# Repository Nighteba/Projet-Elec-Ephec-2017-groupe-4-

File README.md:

# Projet-Elec-Ephec-2017-groupe-4-
Projet d'électro

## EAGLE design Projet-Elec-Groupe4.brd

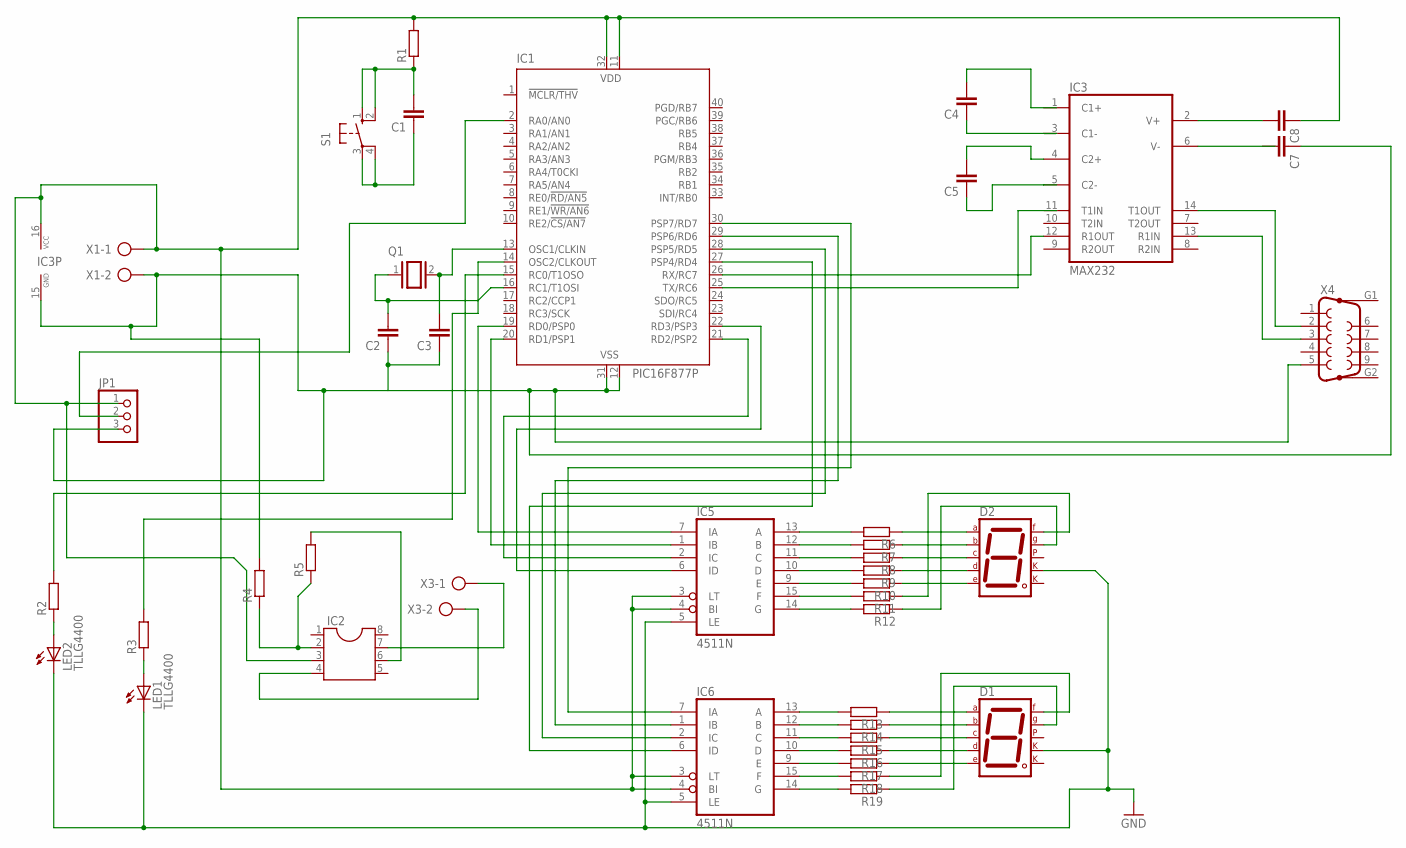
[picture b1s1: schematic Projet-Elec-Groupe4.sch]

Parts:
C1: C-EU025-025X050; C025-025X050
C2, C3, C4, C5, C7, C8: C-EU025-024X044; C025-024X044
D1, D2: 7SEG-CK; 7SEG-13
IC1: PIC16F877P; DIL40
IC2: DIL8; DIL08
IC3: MAX232; DIL16
IC5, IC6: 4511N; DIL16
JP1: PINHD-1X3; 1X03
LED1, LED2: TLLG4400; LED3MM
Q1: XTAL/S; QS
R1, R2, R3, R4, R5, R6, R7, R8, R9, R10, R11, R12, R13, R14, R15, R16, R17, R18, R19: R-EU_0207/10; 0207/10
S1: 10-XX; B3F-10XX
X1, X3: AK300/2
X4: F09HP

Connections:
GND: D1.3 (CK1), D2.3 (CK1), IC5.5 (LE), IC6.5 (LE), LED1.K (C), LED2.K (C)
unnamed: C5.2, IC3.4 (C2+)
unnamed: C2.2, IC1.14 (OSC2/CLKOUT), Q1.1
unnamed: C8.1, IC1.11 (VDD), IC1.32 (VDD), IC2.3, IC3.16 (VCC), IC5.3 (LT), IC5.4 (BI), IC6.3 (LT), IC6.4 (BI), JP1.1, R1.2, X1.1
unnamed: C1.2, R1.1, S1.1 (S), S1.2 (S1)
unnamed: C1.1, S1.3, S1.4 (P1)
unnamed: C5.1, IC3.5 (C2-)
unnamed: C3.2, IC1.13 (OSC1/CLKIN), Q1.2
unnamed: IC1.2 (RA0/AN0), JP1.2
unnamed: IC1.26 (RX/RC7), IC3.12 (R1OUT)
unnamed: IC3.14 (T1OUT), X4.2
unnamed: IC3.13 (R1IN), X4.3
unnamed: C4.1, IC3.3 (C1-)
unnamed: C8.2, IC3.2 (V+)
unnamed: IC5.13 (A), R6.2
unnamed: D2.7 (A), R6.1
unnamed: IC5.12 (B), R7.2
unnamed: D2.6 (B), R7.1
unnamed: IC5.11 (C), R8.2
unnamed: D2.9 (F), R11.1
unnamed: D2.10 (G), R12.1
unnamed: IC2.7, X3.1
unnamed: IC1.19 (RD0/PSP0), IC5.7 (IA)
unnamed: IC1.20 (RD1/PSP1), IC5.1 (IB)
unnamed: IC1.21 (RD2/PSP2), IC5.2 (IC)
unnamed: IC1.22 (RD3/PSP3), IC5.6 (ID)
unnamed: IC6.13 (A), R13.2
unnamed: D1.7 (A), R13.1
unnamed: D1.6 (B), R14.1
unnamed: IC6.12 (B), R14.2
unnamed: IC6.11 (C), R15.2
unnamed: IC1.27 (PSP4/RD4), IC6.6 (ID)
unnamed: IC1.28 (PSP5/RD5), IC6.2 (IC)
unnamed: IC1.29 (PSP6/RD6), IC6.1 (IB)
unnamed: IC1.30 (PSP7/RD7), IC6.7 (IA)
unnamed: IC1.15 (RC0/T1OSO), R2.2
unnamed: LED2.A, R2.1
unnamed: IC2.4, X3.2
unnamed: IC2.2, R4.1, R5.1
unnamed: LED1.A, R3.1
unnamed: IC2.6, R5.2
unnamed: D2.4 (C), R8.1
unnamed: D1.9 (F), R18.1
unnamed: D1.10 (G), R19.1
unnamed: IC5.10 (D), R9.2
unnamed: D2.2 (D), R9.1
unnamed: IC5.9 (E), R10.2
unnamed: D2.1 (E), R10.1
unnamed: IC5.15 (F), R11.2
unnamed: IC5.14 (G), R12.2
unnamed: IC6.10 (D), R16.2
unnamed: IC6.9 (E), R17.2
unnamed: IC6.15 (F), R18.2
unnamed: IC6.14 (G), R19.2
unnamed: D1.4 (C), R15.1
unnamed: D1.2 (D), R16.1
unnamed: D1.1 (E), R17.1
unnamed: IC1.16 (RC1/T1OSI), R3.2
unnamed: C2.1, C3.1, C7.1, IC1.12 (VSS), IC1.31 (VSS), IC3.15 (GND), JP1.3, R4.2, X1.2, X4.5
VDD: IC5.16 (VDD), IC6.16 (VDD)
VSS: IC5.8 (VSS), IC6.8 (VSS)

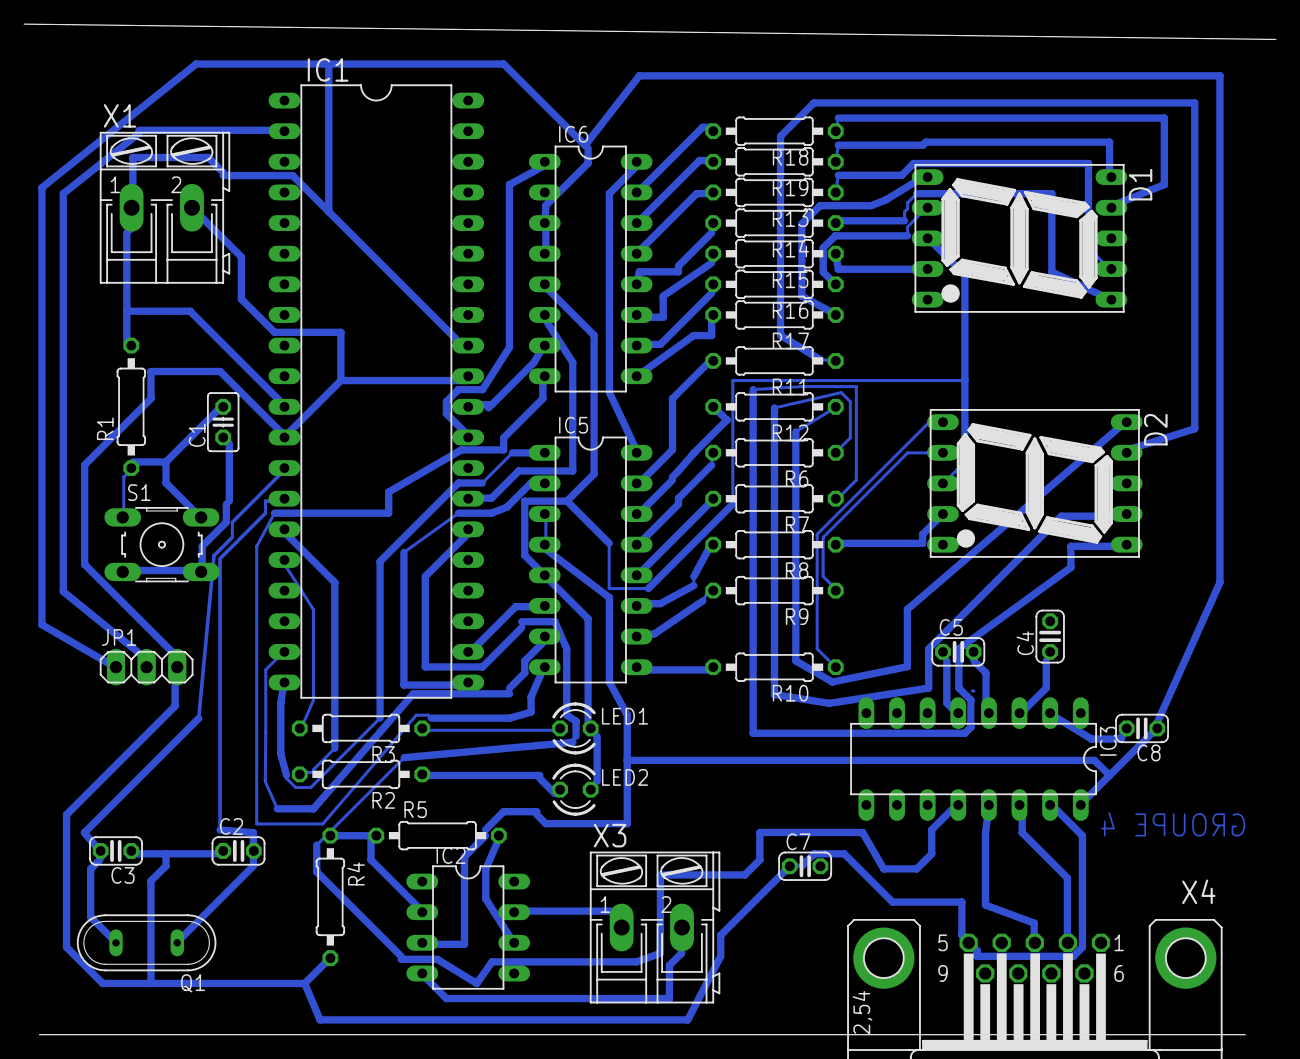
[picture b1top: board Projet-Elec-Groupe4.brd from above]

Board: 2 copper layers, 103.8 x 83.8 mm, 41 parts (0 on the bottom side), 61 nets.

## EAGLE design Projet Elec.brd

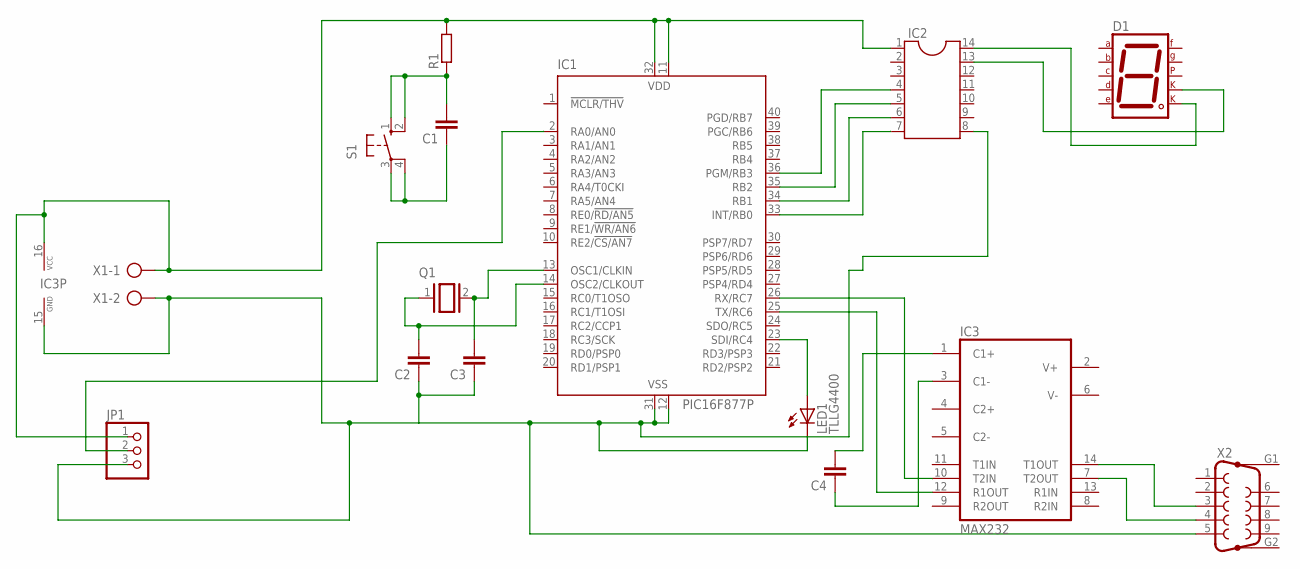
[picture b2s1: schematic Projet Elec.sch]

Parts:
C1: C-EU025-025X050; C025-025X050
C2, C3, C4: C-EU025-024X044; C025-024X044
D1: 7SEG-CK; 7SEG-13
IC1: PIC16F877P; DIL40
IC2: DIL14
IC3: MAX232; DIL16
JP1: PINHD-1X3; 1X03
LED1: TLLG4400; LED3MM
Q1: XTAL/S; QS
R1: R-EU_0207/10; 0207/10
S1: 10-XX; B3F-10XX
X1: AK300/2
X2: F09VP

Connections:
unnamed: IC1.11 (VDD), IC1.32 (VDD), IC2.1, IC3.16 (VCC), JP1.1, R1.2, X1.1
unnamed: C2.2, IC1.14 (OSC2/CLKOUT), Q1.1
unnamed: C2.1, C3.1, IC1.12 (VSS), IC1.31 (VSS), IC2.8, IC3.15 (GND), JP1.3, LED1.K (C), X1.2, X2.5
unnamed: C1.2, R1.1, S1.1 (S), S1.2 (S1)
unnamed: C1.1, S1.3, S1.4 (P1)
unnamed: C3.2, IC1.13 (OSC1/CLKIN), Q1.2
unnamed: IC1.2 (RA0/AN0), JP1.2
unnamed: IC1.23 (SDI/RC4), LED1.A
unnamed: IC1.25 (TX/RC6), IC3.12 (R1OUT)
unnamed: IC1.26 (RX/RC7), IC3.10 (T2IN)
unnamed: IC1.33 (INT/RB0), IC2.7
unnamed: IC1.34 (RB1), IC2.6
unnamed: IC1.35 (RB2), IC2.5
unnamed: IC1.36 (PGM/RB3), IC2.4
unnamed: D1.3 (CK1), IC2.13
unnamed: D1.8 (CK2), IC2.14
unnamed: IC3.14 (T1OUT), X2.3
unnamed: IC3.7 (T2OUT), X2.4
unnamed: C4.2, IC3.1 (C1+)
unnamed: C4.1, IC3.3 (C1-)

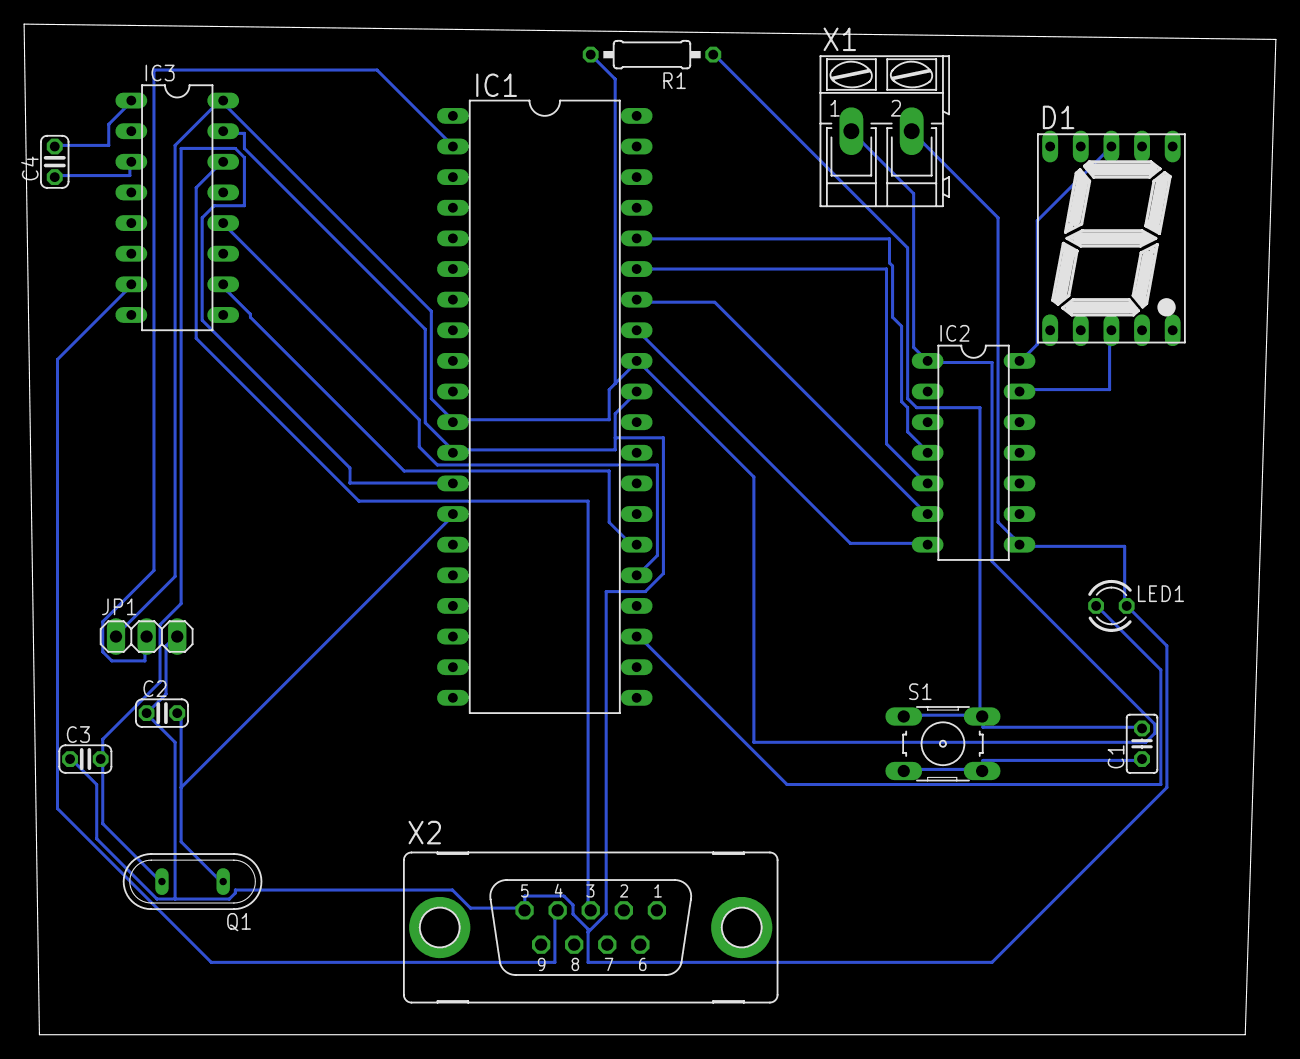
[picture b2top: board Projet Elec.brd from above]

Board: 2 copper layers, 103.8 x 83.8 mm, 15 parts (0 on the bottom side), 20 nets.

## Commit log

2017-03-07 Add the report files
2017-03-08 Last changes
2017-05-11 Create BiSerialCom
2017-05-11 Create SerialPortReader
2017-05-11 Create SerialPortWriter
2017-05-11 Update SerialPortReader
2017-05-12 Update SerialPortWriter
2017-05-14 Create ElectroGUI
2017-05-14 Update BiSerialCom
2017-05-14 Update ElectroGUI
2017-05-15 Create SDLinearGradientPanel
2017-05-15 Update SDLinearGradientPanel
    Fenetre avec gradient pour faire plus classe, si le temps le permet....
